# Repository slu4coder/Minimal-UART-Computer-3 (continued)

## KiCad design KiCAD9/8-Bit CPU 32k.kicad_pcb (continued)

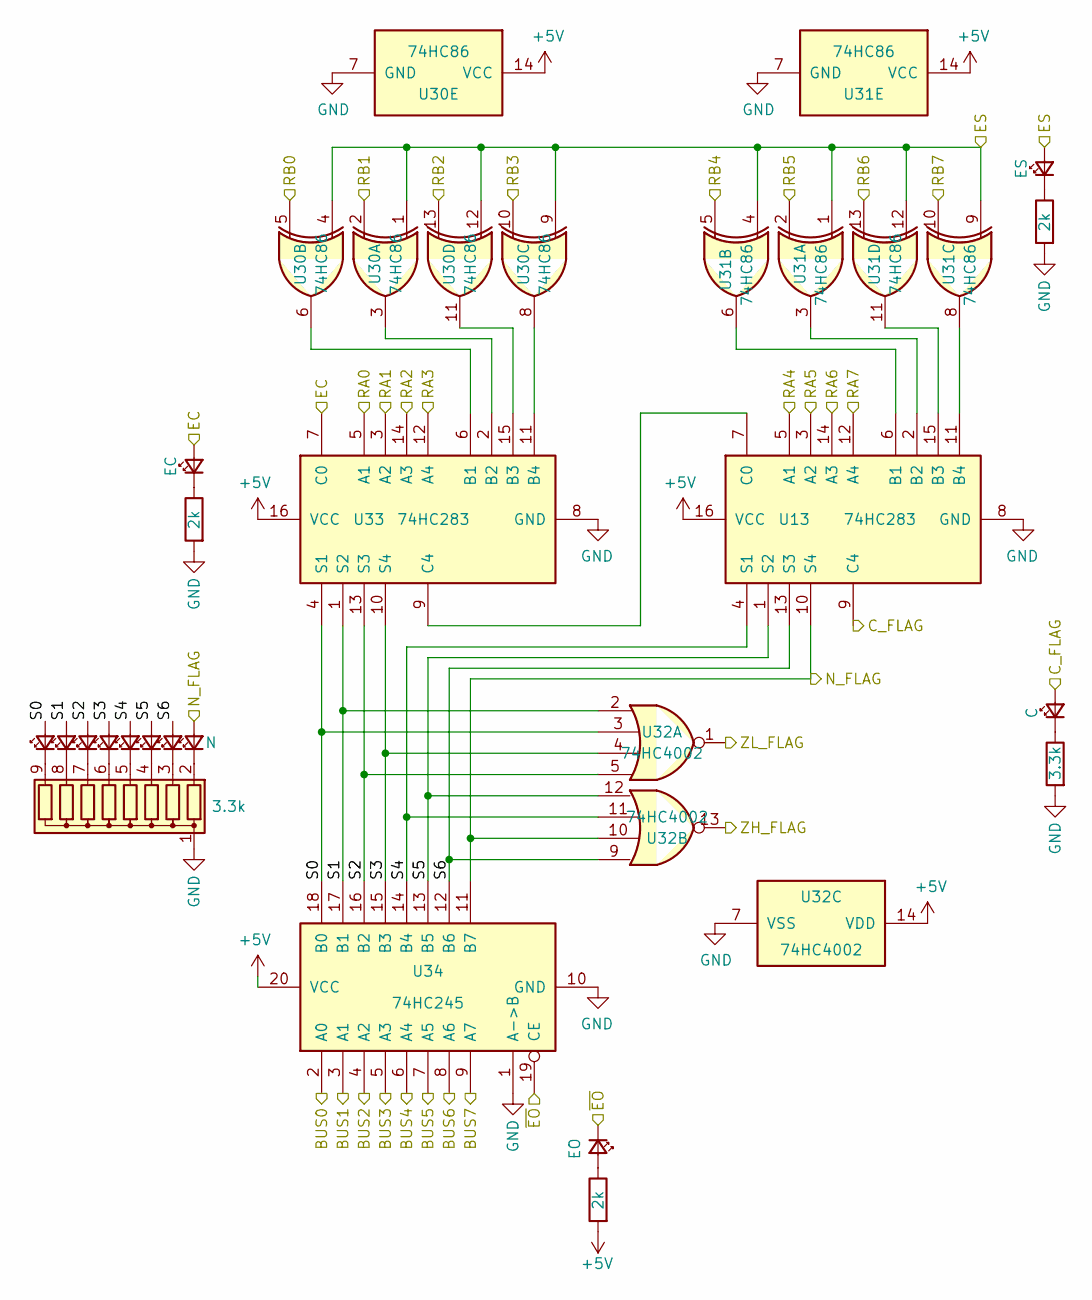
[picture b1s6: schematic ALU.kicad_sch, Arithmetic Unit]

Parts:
D52, D53, D54, D55, D56, D57, D58: LED_Small; LED_D5.0mm
D59: N; LED_D5.0mm
D78: EO; LED_D5.0mm
D93: EC; LED_D5.0mm
D94: ES; LED_D5.0mm
D95: C; LED_D5.0mm
R11, R26, R27: 2k; R_Axial_DIN0207_L6.3mm_D2.5mm_P7.62mm_Horizontal
R28: 3.3k; R_Axial_DIN0207_L6.3mm_D2.5mm_P7.62mm_Horizontal
RN8: 3.3k; R_Array_SIP9
U13, U33: 74HC283; DIP-16_W7.62mm
U30, U31: 74HC86; DIP-14_W7.62mm
U32: 74HC4002; DIP-14_W7.62mm
U34: 74HC245; DIP-20_W7.62mm

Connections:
+5V: R11.2, U13.16 (VCC), U30.14 (VCC), U31.14 (VCC), U32.14 (VDD), U33.16 (VCC), U34.20 (VCC); also elsewhere on the board
/ALU/BUS0: U34.2 (A0); also elsewhere on the board
/ALU/BUS1: U34.3 (A1); also elsewhere on the board
/ALU/BUS2: U34.4 (A2); also elsewhere on the board
/ALU/BUS3: U34.5 (A3); also elsewhere on the board
/ALU/BUS4: U34.6 (A4); also elsewhere on the board
/ALU/BUS5: U34.7 (A5); also elsewhere on the board
/ALU/BUS6: U34.8 (A6); also elsewhere on the board
/ALU/BUS7: U34.9 (A7); also elsewhere on the board
/ALU/C_FLAG: D95.2 (A), U13.9 (C4); also elsewhere on the board
/ALU/EC: D93.2 (A), U33.7 (C0); also elsewhere on the board
/ALU/ES: D94.2 (A), U30.1, U30.4, U30.9, U30.12, U31.1, U31.4, U31.9, U31.12; also elsewhere on the board
/ALU/N_FLAG: D59.2 (A), U13.10 (S4), U32.10, U34.11 (B7); also elsewhere on the board
/ALU/RA0: U33.5 (A1); also elsewhere on the board
/ALU/RA1: U33.3 (A2); also elsewhere on the board
/ALU/RA2: U33.14 (A3); also elsewhere on the board
/ALU/RA3: U33.12 (A4); also elsewhere on the board
/ALU/RA4: U13.5 (A1); also elsewhere on the board
/ALU/RA5: U13.3 (A2); also elsewhere on the board
/ALU/RA6: U13.14 (A3); also elsewhere on the board
/ALU/RA7: U13.12 (A4); also elsewhere on the board
/ALU/RB0: U30.5; also elsewhere on the board
/ALU/RB1: U30.2; also elsewhere on the board
/ALU/RB2: U30.13; also elsewhere on the board
/ALU/RB3: U30.10; also elsewhere on the board
/ALU/RB4: U31.5; also elsewhere on the board
/ALU/RB5: U31.2; also elsewhere on the board
/ALU/RB6: U31.13; also elsewhere on the board
/ALU/RB7: U31.10; also elsewhere on the board
/ALU/S0: D52.2 (A), U32.3, U33.4 (S1), U34.18 (B0)
/ALU/S1: D53.2 (A), U32.2, U33.1 (S2), U34.17 (B1)
/ALU/S2: D54.2 (A), U32.5, U33.13 (S3), U34.16 (B2)
/ALU/S3: D55.2 (A), U32.4, U33.10 (S4), U34.15 (B3)
/ALU/S4: D56.2 (A), U13.4 (S1), U32.11, U34.14 (B4)
/ALU/S5: D57.2 (A), U13.1 (S2), U32.12, U34.13 (B5)
/ALU/S6: D58.2 (A), U13.13 (S3), U32.9, U34.12 (B6)
/ALU/ZH_FLAG: U32.13; also elsewhere on the board
/ALU/ZL_FLAG: U32.1; also elsewhere on the board
/ALU/~EO: D78.1 (K), U34.19 (CE); also elsewhere on the board
GND: R26.2, R27.2, R28.2, RN8.1 (common), U13.8 (GND), U30.7 (GND), U31.7 (GND), U32.7 (VSS), U33.8 (GND), U34.1 (A->B), U34.10 (GND); also elsewhere on the board
unnamed: D52.1 (K), RN8.9 (R8)
unnamed: D53.1 (K), RN8.8 (R7)
unnamed: D54.1 (K), RN8.7 (R6)
unnamed: D55.1 (K), RN8.6 (R5)
unnamed: D56.1 (K), RN8.5 (R4)
unnamed: D57.1 (K), RN8.4 (R3)
unnamed: D58.1 (K), RN8.3 (R2)
unnamed: D59.1 (K), RN8.2 (R1)
unnamed: D78.2 (A), R11.1
unnamed: D93.1 (K), R26.1
unnamed: D94.1 (K), R27.1
unnamed: D95.1 (K), R28.1
unnamed: U13.6 (B1), U31.6
unnamed: U13.2 (B2), U31.3
unnamed: U13.15 (B3), U31.11
unnamed: U13.11 (B4), U31.8
unnamed: U13.7 (C0), U33.9 (C4)
unnamed: U30.6, U33.6 (B1)
unnamed: U30.3, U33.2 (B2)
unnamed: U30.11, U33.15 (B3)
unnamed: U30.8, U33.11 (B4)

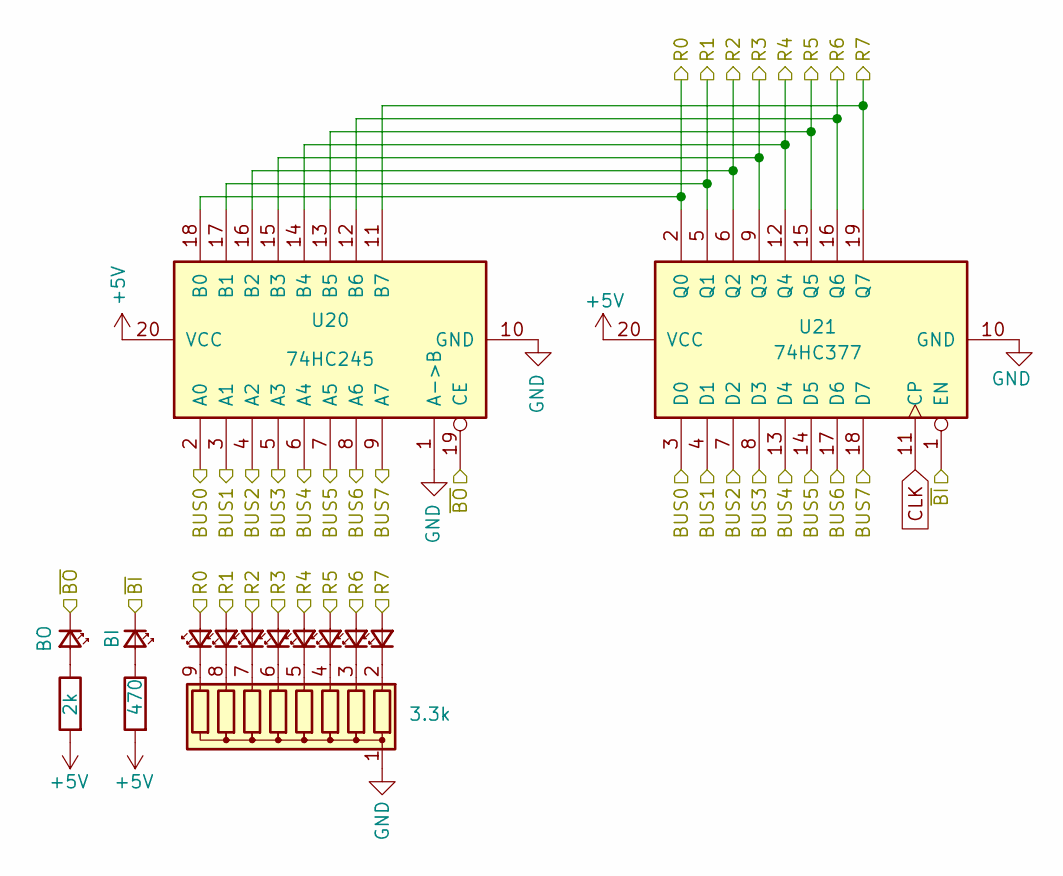
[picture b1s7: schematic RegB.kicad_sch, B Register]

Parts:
D44, D45, D46, D47, D48, D49, D50, D51: LED_Small; LED_D5.0mm
D76: BI; LED_D5.0mm
D77: BO; LED_D5.0mm
R9: 470; R_Axial_DIN0207_L6.3mm_D2.5mm_P7.62mm_Horizontal
R10: 2k; R_Axial_DIN0207_L6.3mm_D2.5mm_P7.62mm_Horizontal
RN7: 3.3k; R_Array_SIP9
U20: 74HC245; DIP-20_W7.62mm
U21: 74HC377; DIP-20_W7.62mm

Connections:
+5V: R9.2, R10.2, U20.20 (VCC), U21.20 (VCC); also elsewhere on the board
/ALU/BUS0: U20.2 (A0), U21.3 (D0); also elsewhere on the board
/ALU/BUS1: U20.3 (A1), U21.4 (D1); also elsewhere on the board
/ALU/BUS2: U20.4 (A2), U21.7 (D2); also elsewhere on the board
/ALU/BUS3: U20.5 (A3), U21.8 (D3); also elsewhere on the board
/ALU/BUS4: U20.6 (A4), U21.13 (D4); also elsewhere on the board
/ALU/BUS5: U20.7 (A5), U21.14 (D5); also elsewhere on the board
/ALU/BUS6: U20.8 (A6), U21.17 (D6); also elsewhere on the board
/ALU/BUS7: U20.9 (A7), U21.18 (D7); also elsewhere on the board
/ALU/RB0: D44.2 (A), U20.18 (B0), U21.2 (Q0); also elsewhere on the board
/ALU/RB1: D45.2 (A), U20.17 (B1), U21.5 (Q1); also elsewhere on the board
/ALU/RB2: D46.2 (A), U20.16 (B2), U21.6 (Q2); also elsewhere on the board
/ALU/RB3: D47.2 (A), U20.15 (B3), U21.9 (Q3); also elsewhere on the board
/ALU/RB4: D48.2 (A), U20.14 (B4), U21.12 (Q4); also elsewhere on the board
/ALU/RB5: D49.2 (A), U20.13 (B5), U21.15 (Q5); also elsewhere on the board
/ALU/RB6: D50.2 (A), U20.12 (B6), U21.16 (Q6); also elsewhere on the board
/ALU/RB7: D51.2 (A), U20.11 (B7), U21.19 (Q7); also elsewhere on the board
/Control Logic/~BI: D76.1 (K), U21.1 (EN); also elsewhere on the board
/Control Logic/~BO: D77.1 (K), U20.19 (CE); also elsewhere on the board
CLK: U21.11 (CP); also elsewhere on the board
GND: RN7.1 (common), U20.1 (A->B), U20.10 (GND), U21.10 (GND); also elsewhere on the board
unnamed: D44.1 (K), RN7.9 (R8)
unnamed: D45.1 (K), RN7.8 (R7)
unnamed: D46.1 (K), RN7.7 (R6)
unnamed: D47.1 (K), RN7.6 (R5)
unnamed: D48.1 (K), RN7.5 (R4)
unnamed: D49.1 (K), RN7.4 (R3)
unnamed: D50.1 (K), RN7.3 (R2)
unnamed: D51.1 (K), RN7.2 (R1)
unnamed: D76.2 (A), R9.1
unnamed: D77.2 (A), R10.1

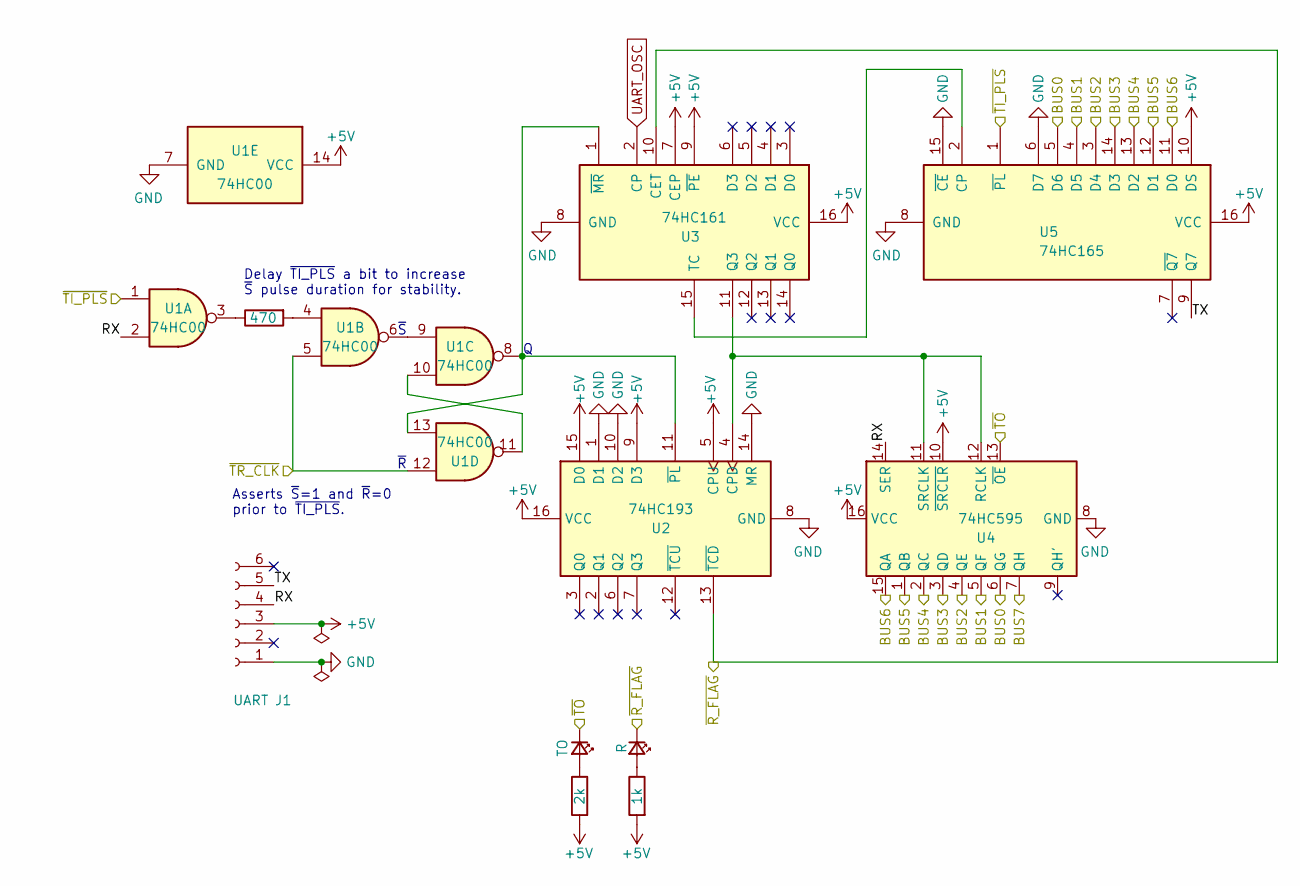
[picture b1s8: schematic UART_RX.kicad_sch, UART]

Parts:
D80: TO; LED_D5.0mm
D97: R; LED_D5.0mm
J1: UART; PinSocket_1x06_P2.54mm_Vertical
R13: 2k; R_Axial_DIN0207_L6.3mm_D2.5mm_P7.62mm_Horizontal
R29: 470; R_Axial_DIN0207_L6.3mm_D2.5mm_P7.62mm_Horizontal
R30: 1k; R_Axial_DIN0207_L6.3mm_D2.5mm_P7.62mm_Horizontal
U1: 74HC00; DIP-14_W7.62mm
U2: 74HC193; DIP-16_W7.62mm
U3: 74HC161; DIP-16_W7.62mm
U4: 74HC595; DIP-16_W7.62mm
U5: 74HC165; DIP-16_W7.62mm

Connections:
+5V: J1.3, R13.2, R30.2, U1.14 (VCC), U2.5 (CPU), U2.9 (D3), U2.15 (D0), U2.16 (VCC), U3.7 (CEP), U3.9 (~PE), U3.16 (VCC), U4.10 (~SRCLR), U4.16 (VCC), U5.10 (DS), U5.16 (VCC); also elsewhere on the board
/ALU/BUS0: U4.6 (QG), U5.5 (D6); also elsewhere on the board
/ALU/BUS1: U4.5 (QF), U5.4 (D5); also elsewhere on the board
/ALU/BUS2: U4.4 (QE), U5.3 (D4); also elsewhere on the board
/ALU/BUS3: U4.3 (QD), U5.14 (D3); also elsewhere on the board
/ALU/BUS4: U4.2 (QC), U5.13 (D2); also elsewhere on the board
/ALU/BUS5: U4.1 (QB), U5.12 (D1); also elsewhere on the board
/ALU/BUS6: U4.15 (QA), U5.11 (D0); also elsewhere on the board
/ALU/BUS7: U4.7 (QH); also elsewhere on the board
/Control Logic/~R_FLAG: D97.1 (K), U2.13 (~TCD), U3.10 (CET); also elsewhere on the board
/Control Logic/~TI_PLS: U1.1, U5.1 (~PL); also elsewhere on the board
/Control Logic/~TO: D80.1 (K), U4.13 (~OE); also elsewhere on the board
/Control Logic/~TR_PLS: U1.5, U1.12; also elsewhere on the board
/UART/RX: J1.4, U1.2, U4.14 (SER)
/UART/TX: J1.5, U5.9 (Q7)
GND: J1.1, U1.7 (GND), U2.1 (D1), U2.8 (GND), U2.10 (D2), U2.14 (MR), U3.8 (GND), U4.8 (GND), U5.6 (D7), U5.8 (GND), U5.15 (~CE); also elsewhere on the board
unnamed: D80.2 (A), R13.1
unnamed: D97.2 (A), R30.1
unnamed: R29.1, U1.3
unnamed: R29.2, U1.4
unnamed: U1.6, U1.9
unnamed: U1.10, U1.11
unnamed: U2.4 (CPD), U3.11 (Q3), U4.11 (SRCLK), U4.12 (RCLK)
unnamed: U1.8, U1.13, U2.11 (~PL), U3.1 (~MR)
unnamed: U3.15 (TC), U5.2 (CP)
UART_OSC: U3.2 (CP); also elsewhere on the board

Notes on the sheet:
Delay ~{TI_PLS} a bit to increase ~{S} pulse duration for stability.
Asserts ~{S}=1 and ~{R}=0 prior to ~{TI_PLS}.
~{S}
~{R}

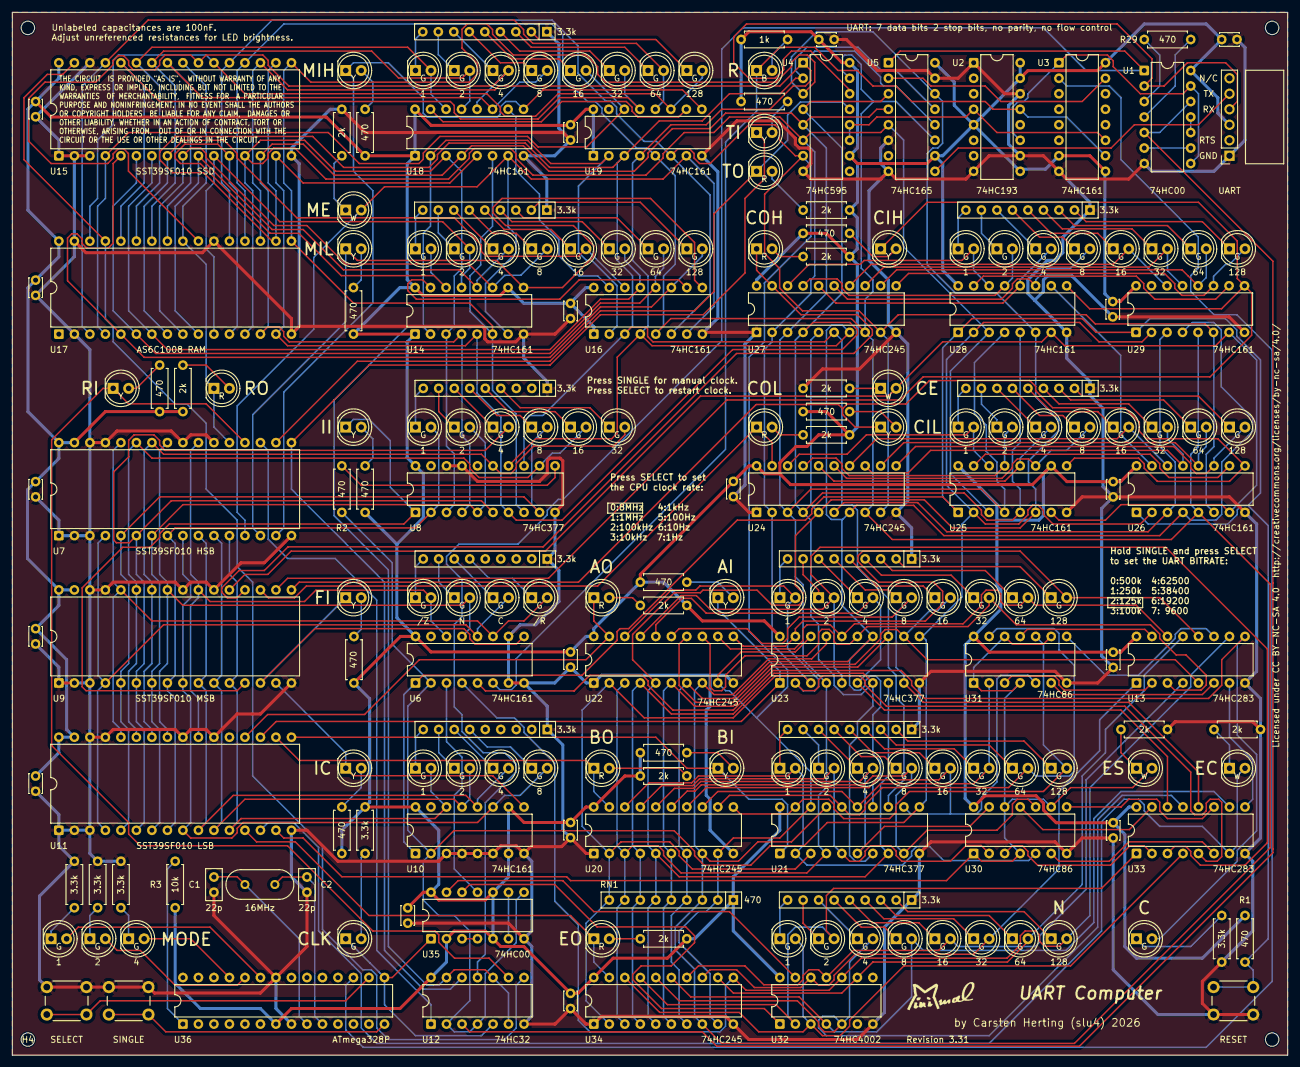
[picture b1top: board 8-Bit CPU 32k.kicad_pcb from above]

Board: 2 copper layers, 208.9 x 170.8 mm, 206 parts (0 on the bottom side), 249 nets.

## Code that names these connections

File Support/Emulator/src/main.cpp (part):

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#define II                0b000000000000000100000000 // MSB
#define FI                0b000000000000001000000000
#define IC                0b000000000000010000000000
#define CIL               0b000000000000100000000000
#define CIH               0b000000000001000000000000
#define COL               0b000000000010000000000000
#define COH               0b000000000100000000000000
#define CE                0b000000001000000000000000
#define ME                0b000000010000000000000000 // HSB
#define MIL               0b000000100000000000000000
#define MIH               0b000001000000000000000000
#define TI                0b000010000000000000000000
#define TO                0b000100000000000000000000
#define TR                0b001000000000000000000000
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
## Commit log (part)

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2025-12-30 Revise README for Minimal UART Computer update
    Updated README to reflect new features and resources.
2026-01-02 Update README with ATmega328p details
    Added detail about ATmega328p used as a variable clock generator.
2026-01-05 Fix makefile formatting and cleanup command
2026-01-05 Add reference to 'Emulator' section in readme
    Added a note to refer to the 'Emulator' section for assembler source code.
2026-01-05 Update readme to specify source code files
2026-01-05 Add initial content to readme.MD
2026-01-24 Fixing a bug in F2 CPU status display
2026-06-09 Clean up README by removing donation section
    Removed donation link and support message from README.
2026-06-13 more playable 'Blocks' game
2026-06-13 improved fps detection
2026-06-13 more playable speed
2026-06-28 bugfix in asm
2026-06-28 bugfix in #emit
2026-06-29 added command line option
2026-06-29 added command line support
2026-06-29 Update title to 'Minimal UART Computer 3'
